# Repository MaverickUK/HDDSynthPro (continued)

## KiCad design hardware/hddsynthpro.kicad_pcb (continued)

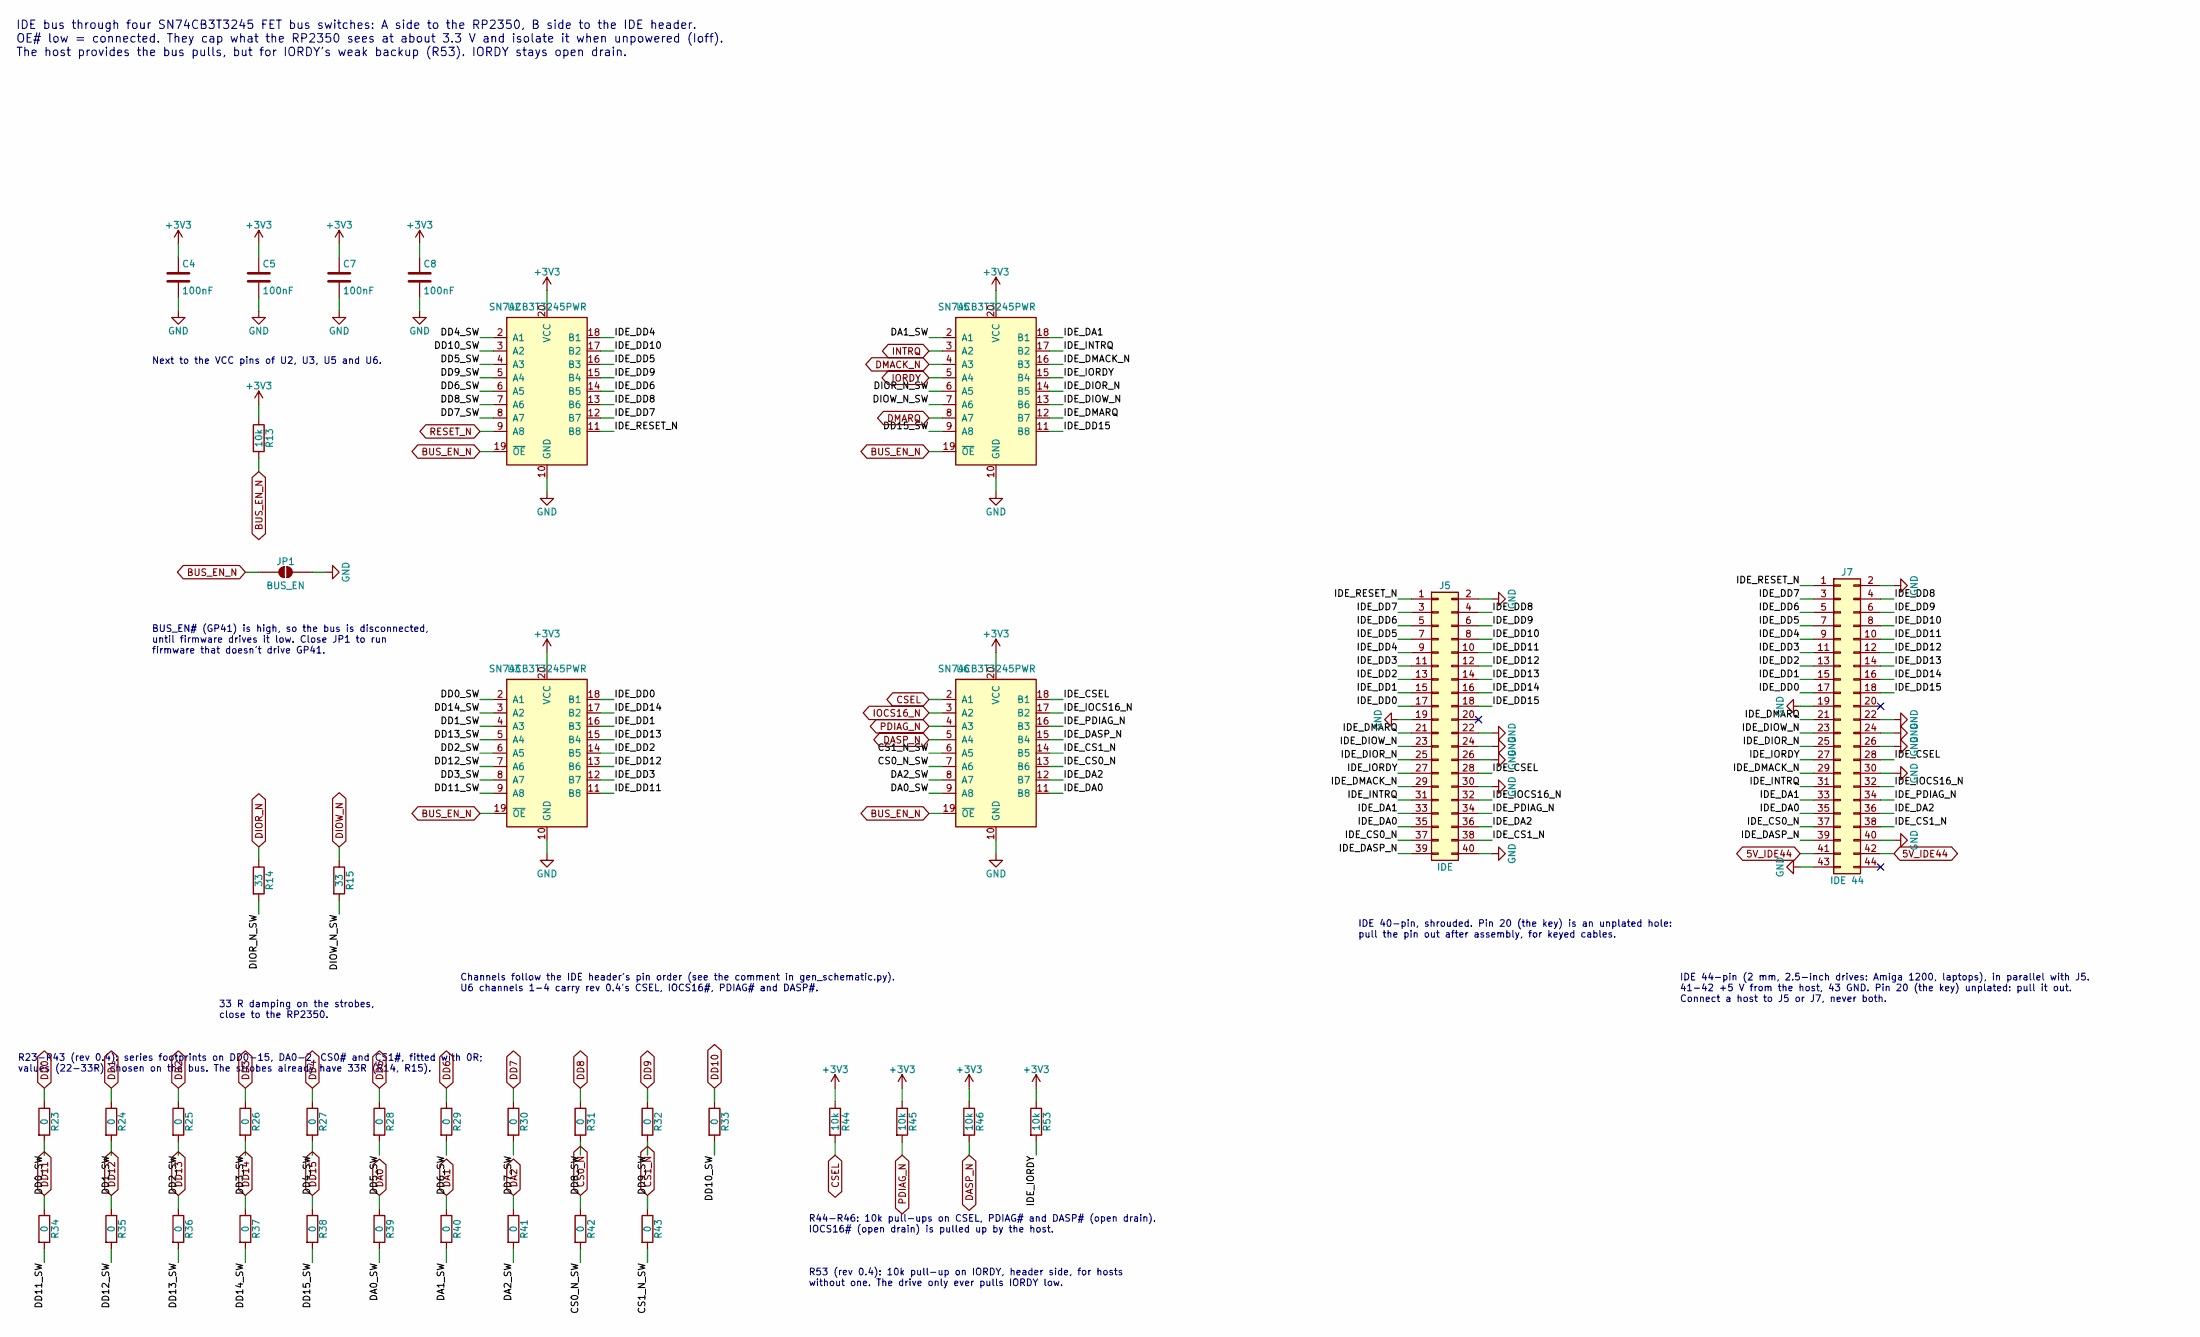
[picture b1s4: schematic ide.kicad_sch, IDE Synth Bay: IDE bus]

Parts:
C4, C5, C7, C8: 100nF; C_0603_1608Metric; LCSC C14663
J5: IDE; IDC-Header_2x20_P2.54mm_Vertical_Pin20Unplated; LCSC C19193815
J7: IDE 44; PinHeader_2x22_P2.00mm_Vertical_Pin20Unplated; LCSC C5371836
JP1: BUS_EN; SolderJumper-2_P1.3mm_Open_RoundedPad1.0x1.5mm
R13: 10k; R_0603_1608Metric; LCSC C25804
R14, R15: 33; R_0603_1608Metric; LCSC C23140
R23, R24, R25, R26, R27, R28, R29, R30, R31, R32, R33, R34, R35, R36, R37, R38, R39, R40, R41, R42, R43: 0; R_0402_1005Metric; LCSC C17168
R44, R45, R46, R53: 10k; R_0402_1005Metric; LCSC C25744
U2, U3, U5, U6: SN74CB3T3245PWR; TSSOP-20_4.4x6.5mm_P0.65mm; LCSC C15298

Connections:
5V_IDE44: J7.41, J7.42; also elsewhere on the board
+3V3: C4.1, C5.1, C7.1, C8.1, R13.1, R44.1, R45.1, R46.1, R53.1, U2.20 (VCC), U3.20 (VCC), U5.20 (VCC), U6.20 (VCC); also elsewhere on the board
/IDE bus/CS0_N_SW: R42.2, U6.7 (A6)
/IDE bus/CS1_N_SW: R43.2, U6.6 (A5)
/IDE bus/DA0_SW: R39.2, U6.9 (A8)
/IDE bus/DA1_SW: R40.2, U5.2 (A1)
/IDE bus/DA2_SW: R41.2, U6.8 (A7)
/IDE bus/DD0_SW: R23.2, U3.2 (A1)
/IDE bus/DD1_SW: R24.2, U3.4 (A3)
/IDE bus/DD2_SW: R25.2, U3.6 (A5)
/IDE bus/DD3_SW: R26.2, U3.8 (A7)
/IDE bus/DD4_SW: R27.2, U2.2 (A1)
/IDE bus/DD5_SW: R28.2, U2.4 (A3)
/IDE bus/DD6_SW: R29.2, U2.6 (A5)
/IDE bus/DD7_SW: R30.2, U2.8 (A7)
/IDE bus/DD8_SW: R31.2, U2.7 (A6)
/IDE bus/DD9_SW: R32.2, U2.5 (A4)
/IDE bus/DD10_SW: R33.2, U2.3 (A2)
/IDE bus/DD11_SW: R34.2, U3.9 (A8)
/IDE bus/DD12_SW: R35.2, U3.7 (A6)
/IDE bus/DD13_SW: R36.2, U3.5 (A4)
/IDE bus/DD14_SW: R37.2, U3.3 (A2)
/IDE bus/DD15_SW: R38.2, U5.9 (A8)
/IDE bus/DIOR_N_SW: R14.2, U5.6 (A5)
/IDE bus/DIOW_N_SW: R15.2, U5.7 (A6)
/IDE bus/IDE_CS0_N: J5.37, J7.37, U6.13 (B6)
/IDE bus/IDE_CS1_N: J5.38, J7.38, U6.14 (B5)
/IDE bus/IDE_CSEL: J5.28, J7.28, U6.18 (B1)
/IDE bus/IDE_DA0: J5.35, J7.35, U6.11 (B8)
/IDE bus/IDE_DA1: J5.33, J7.33, U5.18 (B1)
/IDE bus/IDE_DA2: J5.36, J7.36, U6.12 (B7)
/IDE bus/IDE_DASP_N: J5.39, J7.39, U6.15 (B4)
/IDE bus/IDE_DD0: J5.17, J7.17, U3.18 (B1)
/IDE bus/IDE_DD1: J5.15, J7.15, U3.16 (B3)
/IDE bus/IDE_DD2: J5.13, J7.13, U3.14 (B5)
/IDE bus/IDE_DD3: J5.11, J7.11, U3.12 (B7)
/IDE bus/IDE_DD4: J5.9, J7.9, U2.18 (B1)
/IDE bus/IDE_DD5: J5.7, J7.7, U2.16 (B3)
/IDE bus/IDE_DD6: J5.5, J7.5, U2.14 (B5)
/IDE bus/IDE_DD7: J5.3, J7.3, U2.12 (B7)
/IDE bus/IDE_DD8: J5.4, J7.4, U2.13 (B6)
/IDE bus/IDE_DD9: J5.6, J7.6, U2.15 (B4)
/IDE bus/IDE_DD10: J5.8, J7.8, U2.17 (B2)
/IDE bus/IDE_DD11: J5.10, J7.10, U3.11 (B8)
/IDE bus/IDE_DD12: J5.12, J7.12, U3.13 (B6)
/IDE bus/IDE_DD13: J5.14, J7.14, U3.15 (B4)
/IDE bus/IDE_DD14: J5.16, J7.16, U3.17 (B2)
/IDE bus/IDE_DD15: J5.18, J7.18, U5.11 (B8)
/IDE bus/IDE_DIOR_N: J5.25, J7.25, U5.14 (B5)
/IDE bus/IDE_DIOW_N: J5.23, J7.23, U5.13 (B6)
/IDE bus/IDE_DMACK_N: J5.29, J7.29, U5.16 (B3)
/IDE bus/IDE_DMARQ: J5.21, J7.21, U5.12 (B7)
/IDE bus/IDE_INTRQ: J5.31, J7.31, U5.17 (B2)
/IDE bus/IDE_IOCS16_N: J5.32, J7.32, U6.17 (B2)
/IDE bus/IDE_IORDY: J5.27, J7.27, R53.2, U5.15 (B4)
/IDE bus/IDE_PDIAG_N: J5.34, J7.34, U6.16 (B3)
/IDE bus/IDE_RESET_N: J5.1, J7.1, U2.11 (B8)
BUS_EN_N: JP1.1 (A), R13.2, U2.19 (~OE), U3.19 (~OE), U5.19 (~OE), U6.19 (~OE); also elsewhere on the board
CS0_N: R42.1; also elsewhere on the board
CS1_N: R43.1; also elsewhere on the board
CSEL: R44.2, U6.2 (A1); also elsewhere on the board
DA0: R39.1; also elsewhere on the board
DA1: R40.1; also elsewhere on the board
DA2: R41.1; also elsewhere on the board
DASP_N: R46.2, U6.5 (A4); also elsewhere on the board
DD0: R23.1; also elsewhere on the board
DD1: R24.1; also elsewhere on the board
DD2: R25.1; also elsewhere on the board
DD3: R26.1; also elsewhere on the board
DD4: R27.1; also elsewhere on the board
DD5: R28.1; also elsewhere on the board
DD6: R29.1; also elsewhere on the board
DD7: R30.1; also elsewhere on the board
DD8: R31.1; also elsewhere on the board
DD9: R32.1; also elsewhere on the board
DD10: R33.1; also elsewhere on the board
DD11: R34.1; also elsewhere on the board
DD12: R35.1; also elsewhere on the board
DD13: R36.1; also elsewhere on the board
DD14: R37.1; also elsewhere on the board
DD15: R38.1; also elsewhere on the board
DIOR_N: R14.1; also elsewhere on the board
DIOW_N: R15.1; also elsewhere on the board
DMACK_N: U5.4 (A3); also elsewhere on the board
DMARQ: U5.8 (A7); also elsewhere on the board
GND: C4.2, C5.2, C7.2, C8.2, J5.2, J5.19, J5.22, J5.24, J5.26, J5.30, J5.40, J7.2, J7.19, J7.22, J7.24, J7.26, J7.30, J7.40, J7.43, JP1.2 (B), U2.10 (GND), U3.10 (GND), U5.10 (GND), U6.10 (GND); also elsewhere on the board
INTRQ: U5.3 (A2); also elsewhere on the board
IOCS16_N: U6.3 (A2); also elsewhere on the board
IORDY: U5.5 (A4); also elsewhere on the board
PDIAG_N: R45.2, U6.4 (A3); also elsewhere on the board
RESET_N: U2.9 (A8); also elsewhere on the board

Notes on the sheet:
IDE bus through four SN74CB3T3245 FET bus switches: A side to the RP2350, B side to the IDE header. OE# low = connected. They cap what the RP2350 sees at about 3.3 V and isolate it when unpowered (Ioff). The host provides the bus pulls, but for IORDY's weak backup (R53). IORDY stays open drain.
Channels follow the IDE header's pin order (see the comment in gen_schematic.py). U6 channels 1-4 carry rev 0.4's CSEL, IOCS16#, PDIAG# and DASP#.
R23-R43 (rev 0.4): series footprints on DD0-15, DA0-2, CS0# and CS1#, fitted with 0R; values (22-33R) chosen on the bus. The strobes already have 33R (R14, R15).
R44-R46: 10k pull-ups on CSEL, PDIAG# and DASP# (open drain). IOCS16# (open drain) is pulled up by the host.
R53 (rev 0.4): 10k pull-up on IORDY, header side, for hosts without one. The drive only ever pulls IORDY low.
33 R damping on the strobes, close to the RP2350.
BUS_EN# (GP41) is high, so the bus is disconnected, until firmware drives it low. Close JP1 to run firmware that doesn't drive GP41.
Next to the VCC pins of U2, U3, U5 and U6.
IDE 40-pin, shrouded. Pin 20 (the key) is an unplated hole: pull the pin out after assembly, for keyed cables.
IDE 44-pin (2 mm, 2.5-inch drives: Amiga 1200, laptops), in parallel with J5. 41-42 +5 V from the host, 43 GND. Pin 20 (the key) unplated: pull it out. Connect a host to J5 or J7, never both.

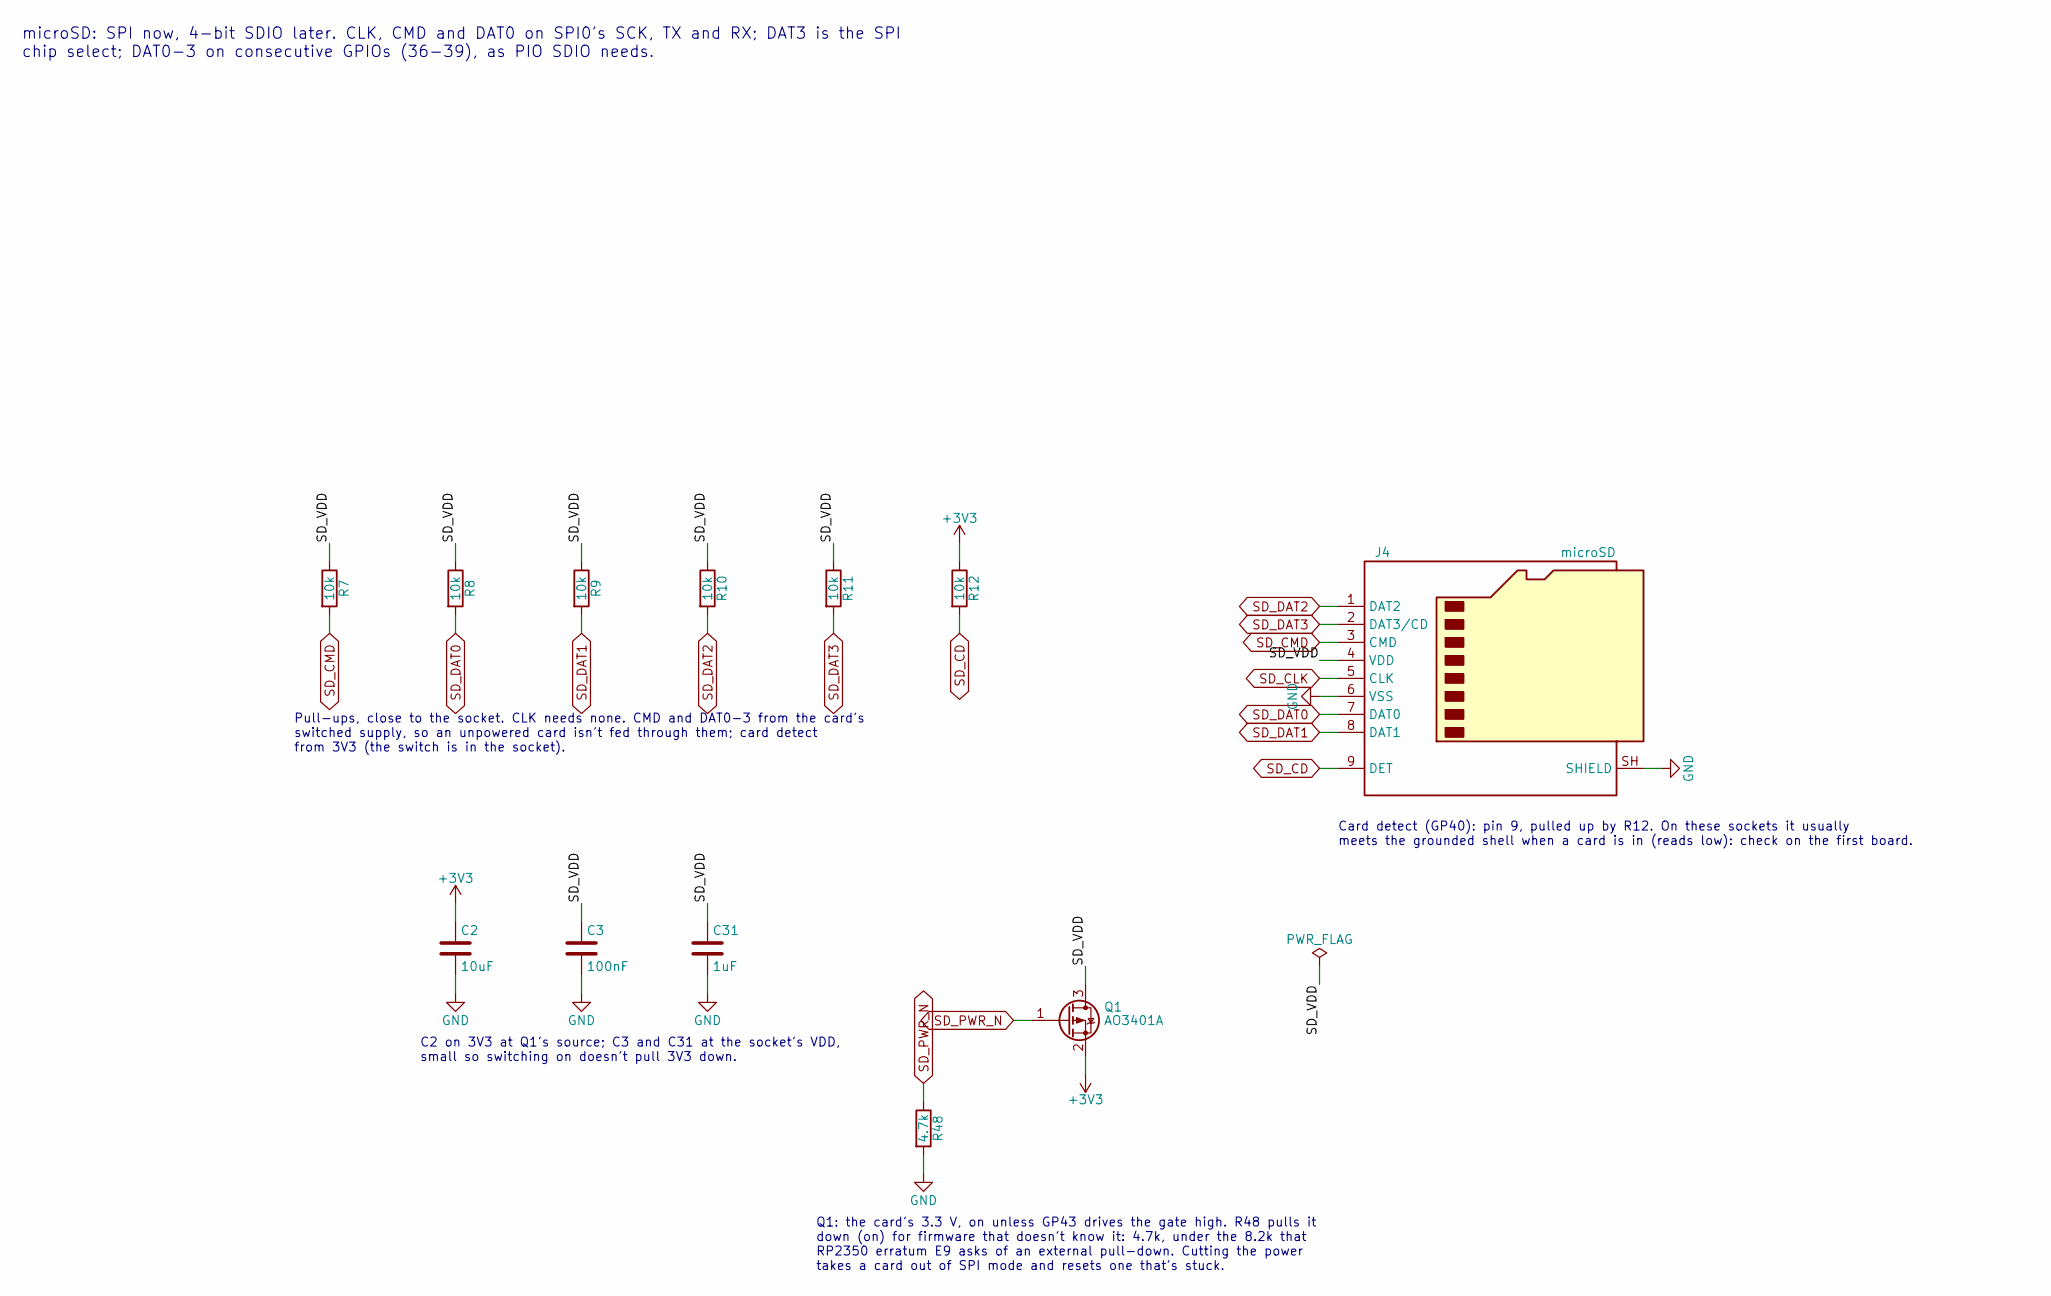
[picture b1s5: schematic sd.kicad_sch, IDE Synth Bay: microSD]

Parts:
C2: 10uF; C_0805_2012Metric; LCSC C15850
C3: 100nF; C_0603_1608Metric; LCSC C14663
C31: 1uF; C_0402_1005Metric; LCSC C52923
J4: microSD; microSD_TF-PUSH; MPN TF PUSH (generic push-push); LCSC C393941
Q1: AO3401A; SOT-23; LCSC C15127
R7, R8, R9, R10, R11, R12: 10k; R_0603_1608Metric; LCSC C25804
R48: 4.7k; R_0402_1005Metric; LCSC C25900

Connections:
+3V3: C2.1, Q1.2 (S), R12.1; also elsewhere on the board
/microSD/SD_VDD: C3.1, C31.1, J4.4 (VDD), Q1.3 (D), R7.1, R8.1, R9.1, R10.1, R11.1
GND: C2.2, C3.2, C31.2, J4.6 (VSS), J4.SH (SHIELD), R48.2; also elsewhere on the board
SD_CD: J4.9 (DET), R12.2; also elsewhere on the board
SD_CLK: J4.5 (CLK); also elsewhere on the board
SD_CMD: J4.3 (CMD), R7.2; also elsewhere on the board
SD_DAT0: J4.7 (DAT0), R8.2; also elsewhere on the board
SD_DAT1: J4.8 (DAT1), R9.2; also elsewhere on the board
SD_DAT2: J4.1 (DAT2), R10.2; also elsewhere on the board
SD_DAT3: J4.2 (DAT3/CD), R11.2; also elsewhere on the board
SD_PWR_N: Q1.1 (G), R48.1; also elsewhere on the board

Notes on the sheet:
microSD: SPI now, 4-bit SDIO later. CLK, CMD and DAT0 on SPI0's SCK, TX and RX; DAT3 is the SPI chip select; DAT0-3 on consecutive GPIOs (36-39), as PIO SDIO needs.
Card detect (GP40): pin 9, pulled up by R12. On these sockets it usually meets the grounded shell when a card is in (reads low): check on the first board.
Pull-ups, close to the socket. CLK needs none. CMD and DAT0-3 from the card's switched supply, so an unpowered card isn't fed through them; card detect from 3V3 (the switch is in the socket).
Q1: the card's 3.3 V, on unless GP43 drives the gate high. R48 pulls it down (on) for firmware that doesn't know it: 4.7k, under the 8.2k that RP2350 erratum E9 asks of an external pull-down. Cutting the power takes a card out of SPI mode and resets one that's stuck.
C2 on 3V3 at Q1's source; C3 and C31 at the socket's VDD, small so switching on doesn't pull 3V3 down.

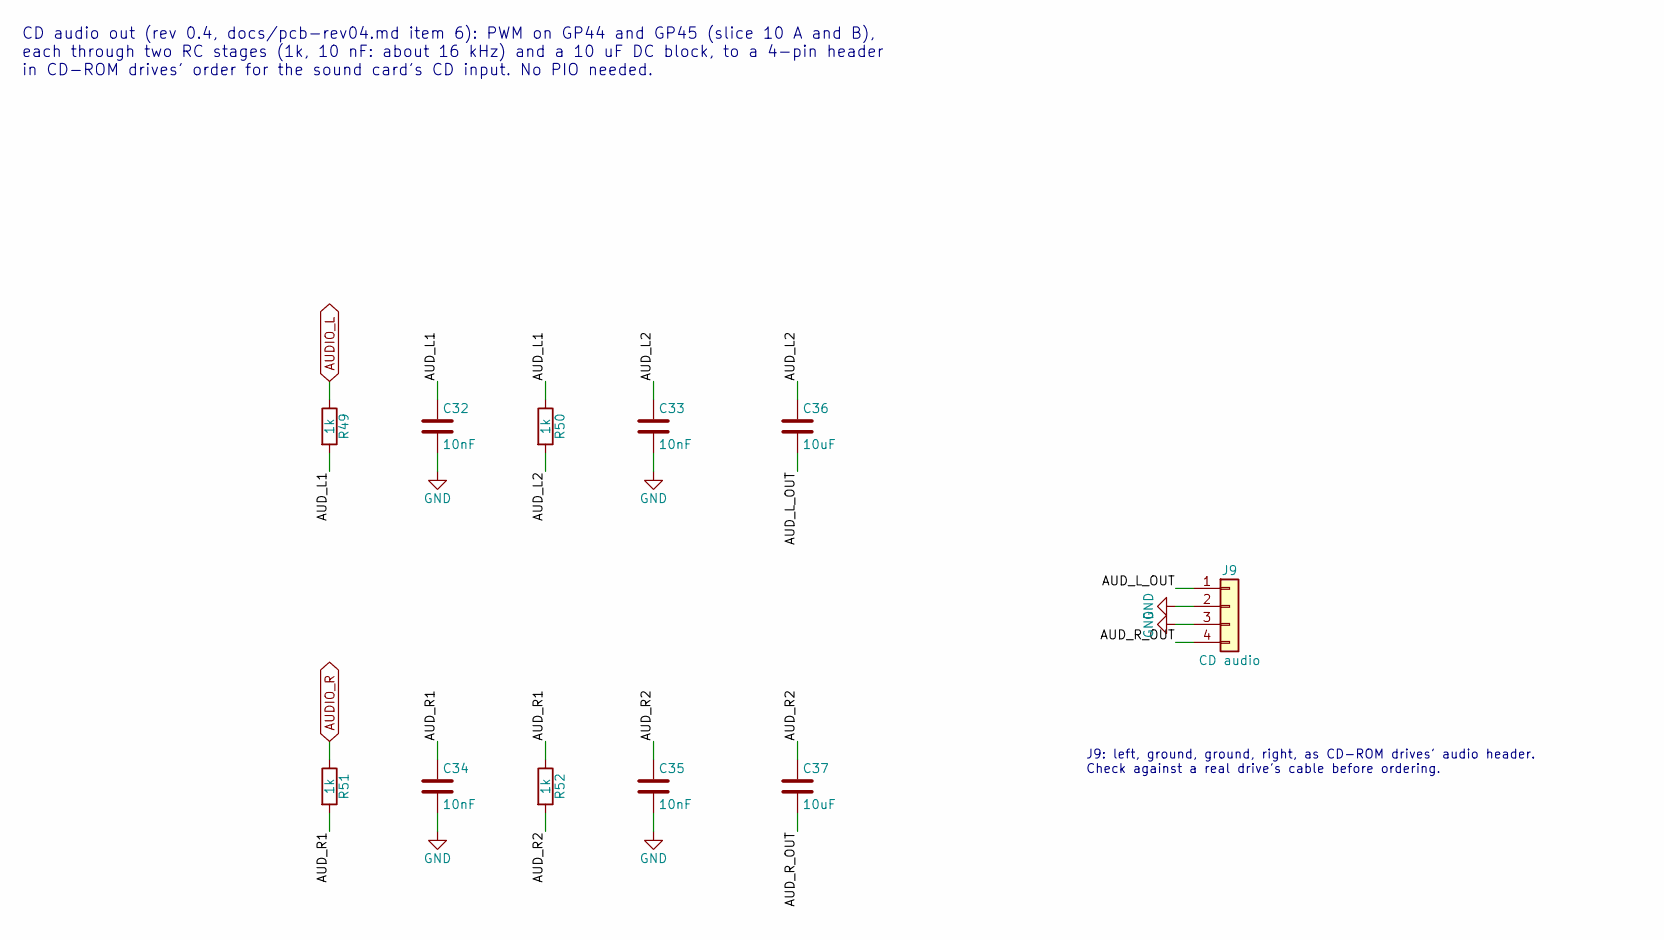
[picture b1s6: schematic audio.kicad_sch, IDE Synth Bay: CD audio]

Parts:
C32, C33, C34, C35: 10nF; C_0402_1005Metric; LCSC C15195
C36, C37: 10uF; C_0805_2012Metric; LCSC C15850
J9: CD audio; PinHeader_1x04_P2.54mm_Vertical
R49, R50, R51, R52: 1k; R_0402_1005Metric; LCSC C11702

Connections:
/CD audio/AUD_L1: C32.1, R49.2, R50.1
/CD audio/AUD_L2: C33.1, C36.1, R50.2
/CD audio/AUD_L_OUT: C36.2, J9.1
/CD audio/AUD_R1: C34.1, R51.2, R52.1
/CD audio/AUD_R2: C35.1, C37.1, R52.2
/CD audio/AUD_R_OUT: C37.2, J9.4
AUDIO_L: R49.1; also elsewhere on the board
AUDIO_R: R51.1; also elsewhere on the board
GND: C32.2, C33.2, C34.2, C35.2, J9.2, J9.3; also elsewhere on the board

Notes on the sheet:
CD audio out (rev 0.4, docs/pcb-rev04.md item 6): PWM on GP44 and GP45 (slice 10 A and B), each through two RC stages (1k, 10 nF: about 16 kHz) and a 10 uF DC block, to a 4-pin header in CD-ROM drives' order for the sound card's CD input. No PIO needed.
J9: left, ground, ground, right, as CD-ROM drives' audio header. Check against a real drive's cable before ordering.

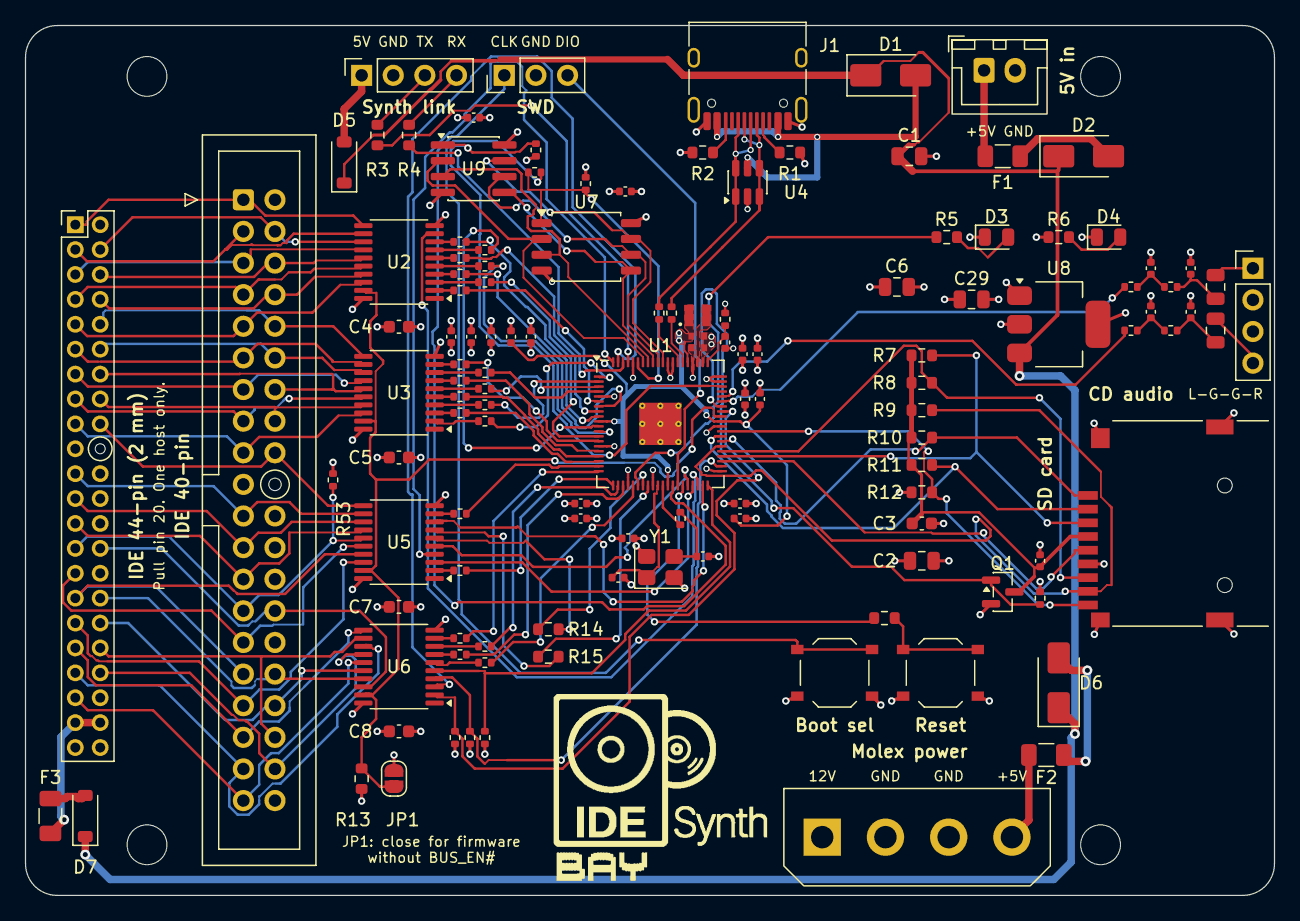
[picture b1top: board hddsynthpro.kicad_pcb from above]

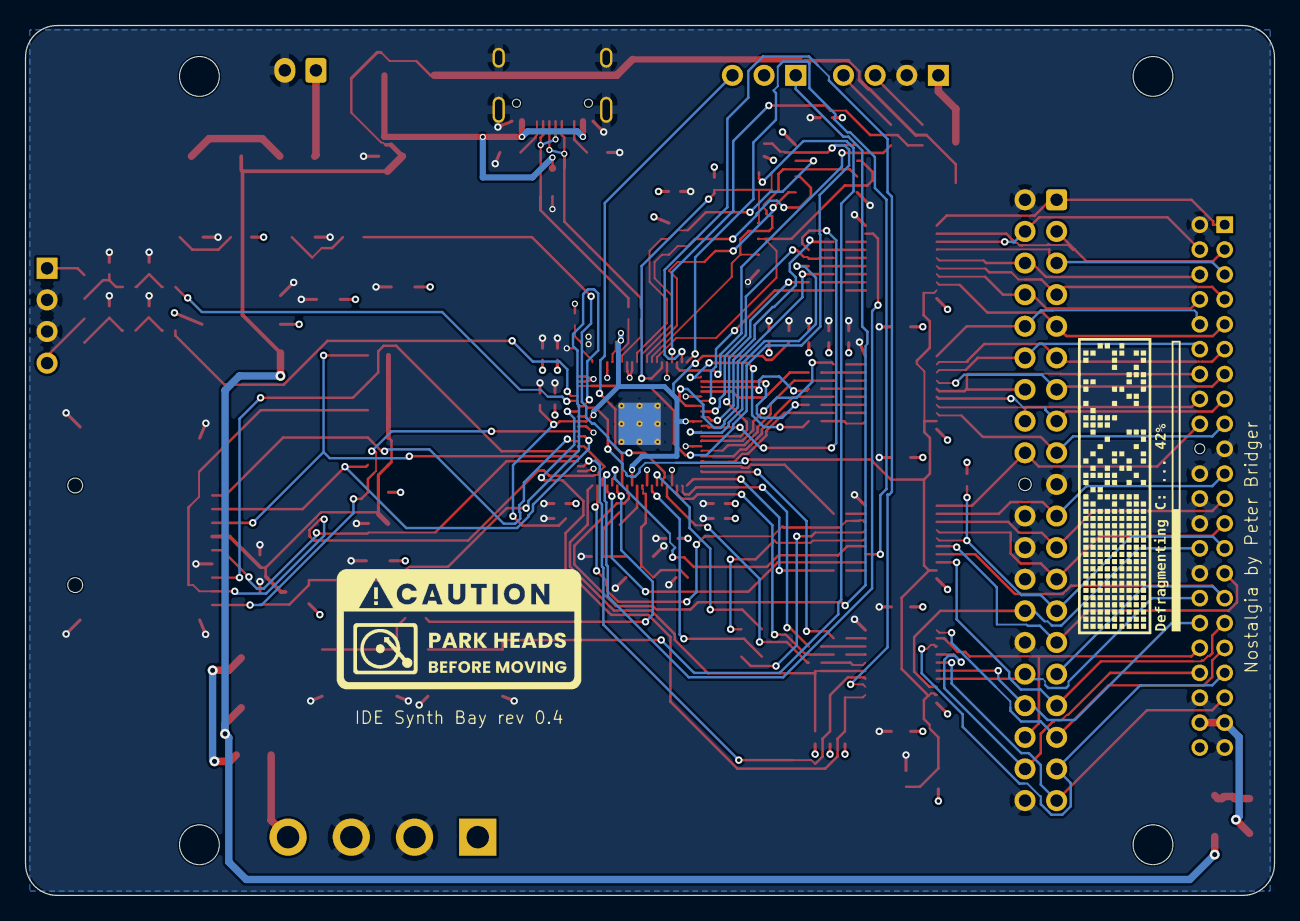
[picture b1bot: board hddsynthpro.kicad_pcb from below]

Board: 4 copper layers, 100.3 x 69.9 mm, 131 parts (2 on the bottom side), 147 nets.

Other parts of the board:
EGG1: EGG_ParkHeads
EGG2: EGG_Defrag
H1, H2, H3, H4: M3; MountingHole_3.2mm_M3
LOGO1: LOGO_IDESynthBay

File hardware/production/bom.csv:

Designator,Footprint,Quantity,Value,LCSC Part #
"C1, C2, C29, C36, C37, C6",0805,6,10uF,C15850
"C10, C11, C9",0402,3,4.7uF,C23733
"C12, C13, C14, C15, C16, C17, C18, C19, C20, C21, C22, C23, C24, C25, C26, C30",0402,16,100nF,C1525
"C27, C28",0402,2,15pF,C1548
"C3, C4, C5, C7, C8",0603,5,100nF,C14663
C31,0402,1,1uF,C52923
"C32, C33, C34, C35",0402,4,10nF,C15195
"D1, D2, D6",D_SMA,3,SS14,C2480
D3,0805,1,Activity,C2297
D4,0805,1,Power,C84256
"D5, D7",D_SOD-123,2,B5819W,C8598
"F1, F2, F3",1206,3,500mA,C19193043
J1,USB_C_Receptacle_HRO_TYPE-C-31-M-12,1,USB-C,C165948
J2,JST_XH_B2B-XH-A_1x02_P2.50mm_Vertical,1,5V in,C158012
J3,PinSocket_1x04_P2.54mm_Vertical,1,Link,C2718488
J4,microSD_TF-PUSH,1,microSD,C393941
J5,IDC-Header_2x20_P2.54mm_Vertical_Pin20Unplated,1,IDE,C19193815
J6,PinHeader_1x03_P2.54mm_Vertical,1,SWD,C2937625
J7,PinHeader_2x22_P2.00mm_Vertical_Pin20Unplated,1,IDE 44,C5371836
J8,Molex_8981_1x04_P5.08mm_Vertical,1,Disk power,"Molex 8981 style, 4 pins, 5.08 mm"
J9,PinHeader_1x04_P2.54mm_Vertical,1,CD audio,
L1,L_Abracon_AOTA-B201610S3R3,1,3.3uH,C42411119
Q1,SOT-23,1,AO3401A,C15127
"R1, R2",0603,2,5.1k,C23186
"R10, R11, R12, R13, R7, R8, R9",0603,7,10k,C25804
"R14, R15",0603,2,33,C23140
R16,0402,1,33,C25105
"R17, R19, R49, R50, R51, R52",0402,6,1k,C11702
"R18, R44, R45, R46, R47, R53",0402,6,10k,C25744
"R20, R3, R4, R6",0603,4,1k,C21190
"R21, R22",0402,2,27,C25100
"R23, R24, R25, R26, R27, R28, R29, R30, R31, R32, R33, R34, R35, R36, R37, R38, R39, R40, R41, R42, R43",0402,21,0,C17168
R48,0402,1,4.7k,C25900
R5,0603,1,470,C23179
SW1,SW_Push_1P1T_XKB_TS-1187A,1,BOOTSEL,C318884
SW2,SW_Push_1P1T_XKB_TS-1187A,1,RESET,C318884
U1,QFN-80-1EP_10x10mm_P0.4mm_EP3.4x3.4mm_ThermalVias,1,RP2350B,C42415655
"U2, U3, U5, U6",TSSOP-20_4.4x6.5mm_P0.65mm,4,SN74CB3T3245PWR,C15298
U4,SOT-23-6,1,USBLC6-2SC6,C2687116
U7,SOIC-8_5.3x5.3mm_P1.27mm,1,W25Q128JVSIQ,C97521
U8,SOT-223-3_TabPin2,1,AMS1117-3.3,C6186
U9,SOIC-8_3.9x4.9mm_P1.27mm,1,APS6404L-3SQR-SN,C5333729
Y1,Crystal_SMD_3225-4Pin_3.2x2.5mm,1,12MHz,C20625731

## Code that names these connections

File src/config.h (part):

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// DD, DA and CS# are on consecutive pins so one PIO read captures an access.
constexpr unsigned PIN_DD0 = 4;      // DD0-DD15 on GPIO 4-19
constexpr unsigned PIN_DA0 = 20;     // DA0-DA2 on GPIO 20-22
constexpr unsigned PIN_CS0_N = 23;   // CS0# (ATA "CS1FX-"): command block registers
constexpr unsigned PIN_CS1_N = 24;   // CS1# (ATA "CS3FX-"): control block registers
constexpr unsigned PIN_BOARD_LED = 25;  // on-board LED, not a bus line
constexpr unsigned PIN_DIOR_N = 26;
constexpr unsigned PIN_DIOW_N = 27;
constexpr unsigned PIN_IORDY = 28;   // host pulls up to 5 V via 1k: only ever drive low or release
constexpr unsigned PIN_INTRQ = 29;
constexpr unsigned PIN_RESET_N = 30;

// Multiword DMA's handshake (docs/dma.md). Wired on the PCB, and on the BB48
// rig since 29 Oct 2026 (IDE pin 21 to GPIO 31, pin 29 to GPIO 3). DMARQ is
// driven only during a DMA command; DMACK# isn't read yet (Ultra DMA will).
constexpr unsigned PIN_DMARQ = 31;
constexpr unsigned PIN_DMACK_N = 3;

// IOCS16# (IDE pin 32), for 16-bit ISA cards that pass it to the ISA bus
// (iocs16.pio). Open drain: pulled low while the data register is addressed,
// otherwise released. GPIO 2 is the only free pin in the PIO window (as PCB
// rev 0.4 plans); the BB48's 2.2k pull-up on it (R17) is harmless for an open
// drain signal the host also pulls up. Wired on the rig since 30 Oct 2026.
constexpr unsigned PIN_IOCS16_N = 2;

// early_answers: core 1 leaves its tight bus loop for the main loop only after
// the bus has been quiet this long, so the host's accesses almost never find it
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// that start off: BUS_EN# held high by a pull-up until the firmware drives it
// low (closing JP1 bypasses it). SD_CD is the card socket's detect switch,
// pulled up, low with a card in (to be checked on the first board).
constexpr unsigned PIN_SD_CD = 40;
constexpr unsigned PIN_BUS_EN_N = 41;

// PCB rev 0.4 (docs/pcb-rev04.md; not used by the firmware yet, unconnected
// on rev 0.3 and the BB48). DASP#, PDIAG# and CSEL go through the bus
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// is the microSD's power switch, pulled down on the board, so the card is
// powered unless the firmware drives it high. AUDIO_L/R are CD audio by PWM
// (slice 10 A and B). PSRAM_CS# is the QSPI PSRAM's chip select (XIP CS1).
constexpr unsigned PIN_DASP_N = 32;
constexpr unsigned PIN_PDIAG_N = 33;
constexpr unsigned PIN_CSEL = 42;
constexpr unsigned PIN_SD_PWR_N = 43;
constexpr unsigned PIN_AUDIO_L = 44;
constexpr unsigned PIN_AUDIO_R = 45;
constexpr unsigned PIN_PSRAM_CS_N = 47;

// Whether `mode = auto` offers multiword DMA where DMARQ is wired is the
// `dma` setting in HDDSYNTH.INI (drive_config::DEFAULT_DMA: off until DMA has
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// The activity link to an HDD Synth (docs/activity-link.md): UART0 TX on
// GPIO 0 ($HDA, $HDE); UART0 RX on GPIO 1, pulled up, for the synth's $HDM
// (protocol version 2, seek_timing = synth).
constexpr unsigned PIN_LINK_TX = 0;
constexpr unsigned PIN_LINK_RX = 1;
constexpr uint32_t LINK_BAUD = 115200;
constexpr uint32_t LINK_HEARTBEAT_MS = 200;  // a sentence at least this often
constexpr uint32_t LINK_HEAD_GAP_US = 2000;  // $HDE at most this often (about its time on the wire)

constexpr unsigned BUS_FIRST_PIN = PIN_DD0;
constexpr unsigned BUS_LAST_PIN = PIN_RESET_N;

// The microSD breakout (slice 5). The same wires serve SPI now and 4-bit
// SDIO later: CLK, CMD and DAT0 are on SPI0's SCK, TX and RX pins, DAT3 is
// the SPI chip select, and DAT0-3 are consecutive, as PIO SDIO needs.
// CMD and DAT0-3 have 10k pull-ups to 3.3 V on the breakout's side.
constexpr unsigned PIN_SD_CLK = 34;   // SPI0 SCK
constexpr unsigned PIN_SD_CMD = 35;   // SPI0 TX (card DI)
constexpr unsigned PIN_SD_DAT0 = 36;  // SPI0 RX (card DO); DAT1-3 on 37-39
constexpr unsigned PIN_SD_DAT3 = 39;  // SPI chip select
// The SPI clock for the card, MHz. SPI0 divides the peripheral clock, which
// main.cpp keeps at the 200 MHz system clock, by an even number, so this
// rounds down: 25 is exact (÷8), the next step is 33.3 (÷6). At 150 MHz (up
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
